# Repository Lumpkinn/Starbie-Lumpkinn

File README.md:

<h1>Project description</h1>
A small motion-controlled digital pet, based off of SharKing's Starbie.

The project has a few differences however, with the most notable ones being the different sprite.

The project itself is basically a mini digital pet, like a tamagotchi, but the main difference is the fact that it responds to movement, and it's environment, instead of just requiring the user to click a few buttons.

Here's a photo of the PCB:
<br>

The Starbie itself is not too dissimilar from SharKing's Starbie</a>, but it has a few differences, with the most obvious one being the new sprite.
(Here's the sprite in question!)->

(And here's a picture of the demo!) -> 

The Starbie is controlled with both the switches on the PCB board, and through how the user moves it around. (If you're looking at the sim, you can simulate this by dragging the starbie in your desired direction.) 

<h1>Materials</h1>
<ul>
  <li>XIAO ESP32 C3</li>
  <li>0.96 OLED</li>
  <li>DHT11</li>
  <li>MX Switches</li>
  <li>Keycaps</li>
  <li>Resistors</li>
  <li>PCB</li>
</ul>
<h2>BOM</h2>

| Item        | Amount | Unit Price  | Total | Vendor |
| ------------- |:-:| :----:|:-----:|:------:|
| XIAO ESP32C6  | 1 | $5.00|$5.00|<a href="https://www.seeedstudio.com/Seeed-XIAO-ESP32C3-p-5431.html">seeedstudio</a>|
| Button Switch SW Cherry MX |2|$0.18|$0.36|<a href="https://www.amazon.com//dp/B0FQP8VYX4">Amazon</a>|
| DHT11 Sensor|1|$1.15|$1.15|<a href="https://www.taydaelectronics.com/dht11-temp-humid-sensor-html.html">Tayda</a>|
|128x64 OLED Display|1|$2.50|$2.50|<a href="https://www.amazon.com/dp/B0GBVWBWCR">Amazon</a>|
|10k Resistor|10|$0.04|$0.40|<a href="https://www.taydaelectronics.com/10-x-resistor-10k-ohm-1w-5-carbon-film-pkg-of-10.html">Tayta</a>|
|MPU6050|1|$2.29|$2.29|<a href="https://www.taydaelectronics.com/mpu-6050-accel-gyro-board.html">Tayda</a>|
|PCB|1|$10.00|$10.00|<a href="https://www.jlcpcb.com/">jlcpcb</a>|
|Keycaps|2|$0.60|$1.20|<a href="https://www.amazon.com/dp/B0CQ2VLMVY">Amazon</a>|
Total: 22.90

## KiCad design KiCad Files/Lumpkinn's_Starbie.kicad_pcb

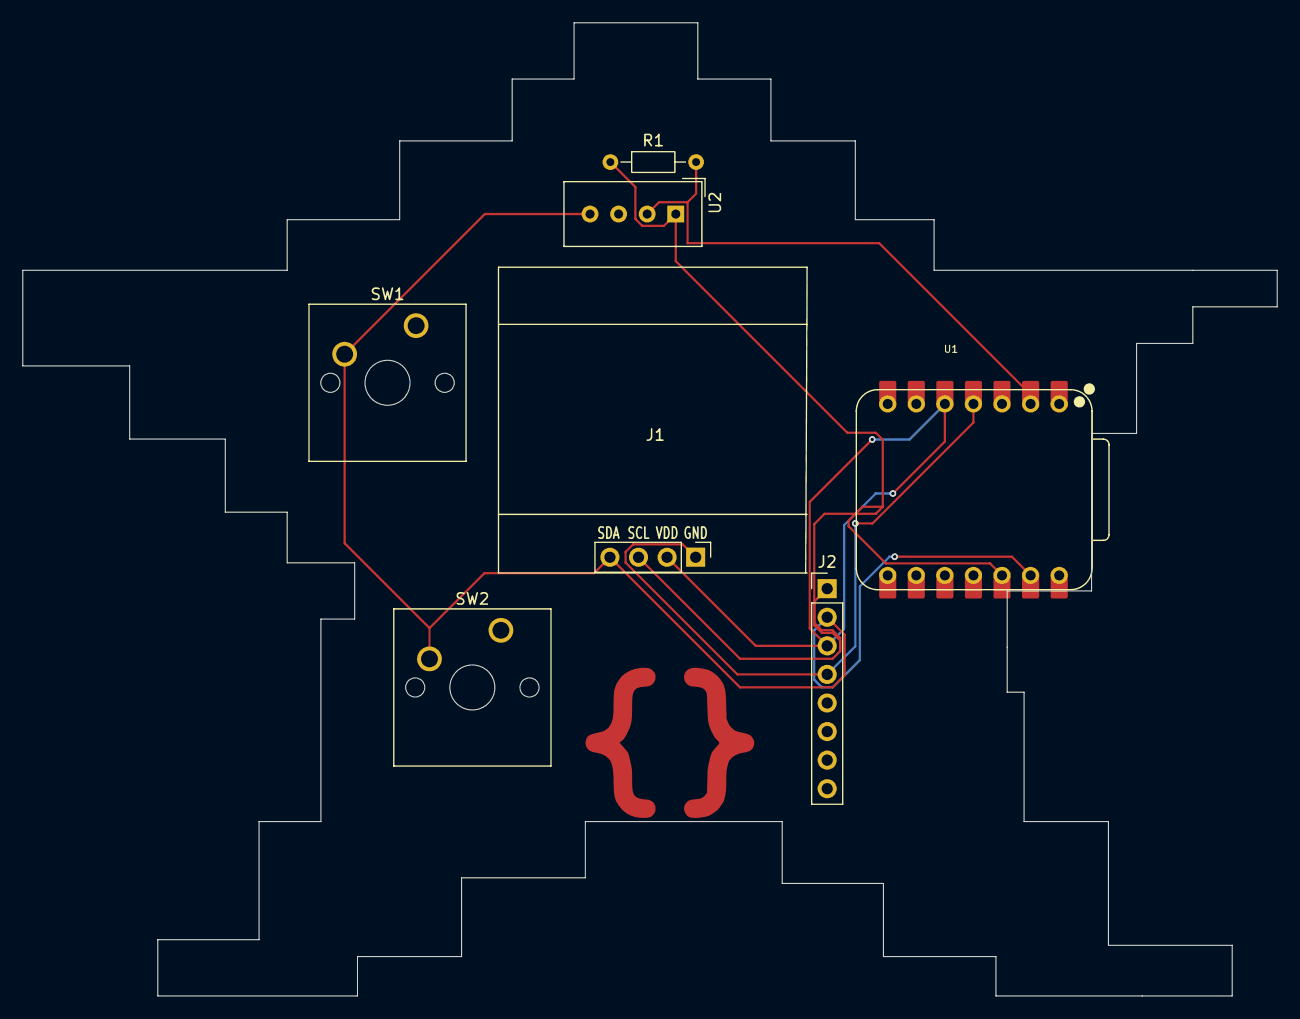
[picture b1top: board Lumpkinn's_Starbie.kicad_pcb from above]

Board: 2 copper layers, 111.5 x 86.5 mm, 7 parts (0 on the bottom side), 5 nets.

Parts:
J1: Conn_01x04_Pin; Display_128x64_096_I2C
J2: Conn_01x08_Pin; PinHeader_1x08_P2.54mm_Vertical
R1: 10k; R_Axial_DIN0204_L3.6mm_D1.6mm_P7.62mm_Horizontal
SW1, SW2: SW_Push; SW_Cherry_MX_1.00u_PCB
U1: XIAO-ESP32-C3-SMD; XIAO-ESP32-C6-DIP
U2: DHT11; Aosong_DHT11_5.5x12.0_P2.54mm

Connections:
+3.3V: J1.3, J2.1, R1.1, U1.12 (3V3_OUT), U2.1 (VDD)
/DHT11 DATA: R1.2, U1.2 (D1), U2.2 (DATA)
/SCL: J1.2, J2.3, U1.5 (D4)
/SDA: J1.1, J2.4, U1.4 (D3)
GND: J1.4, J2.2, SW1.2, SW2.2, U1.13 (GND), U2.4 (GND)
